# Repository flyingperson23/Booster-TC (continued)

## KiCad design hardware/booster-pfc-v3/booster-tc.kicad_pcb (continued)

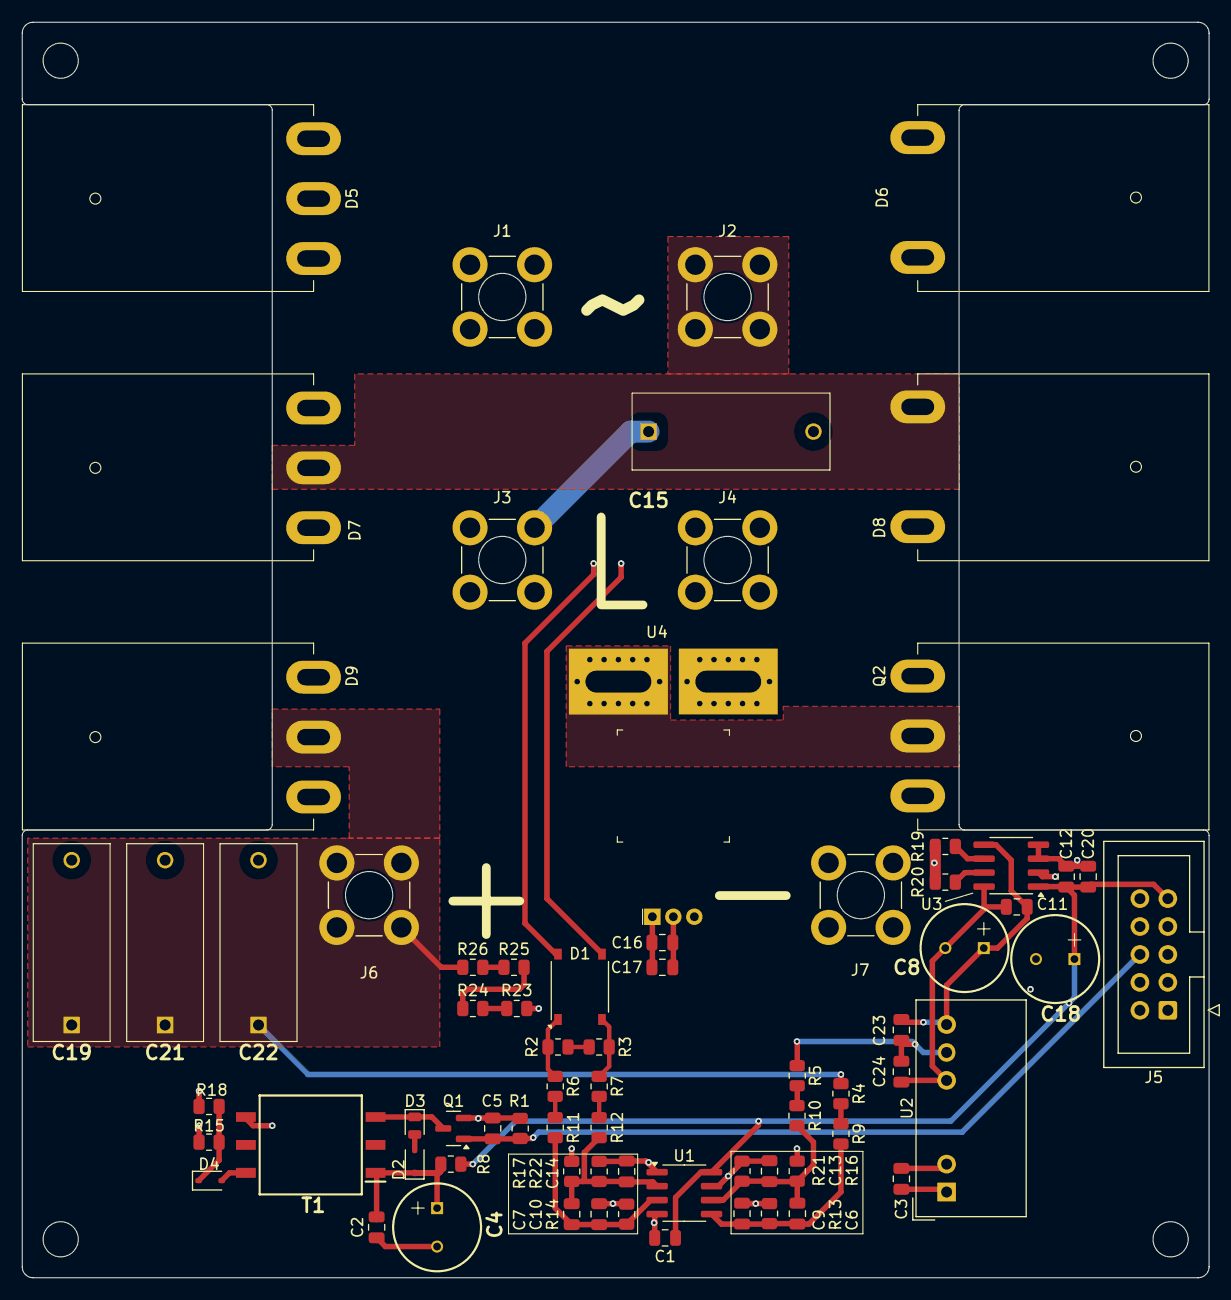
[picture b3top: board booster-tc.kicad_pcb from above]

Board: 4 copper layers, 108.0 x 114.2 mm, 77 parts (0 on the bottom side), 41 nets.

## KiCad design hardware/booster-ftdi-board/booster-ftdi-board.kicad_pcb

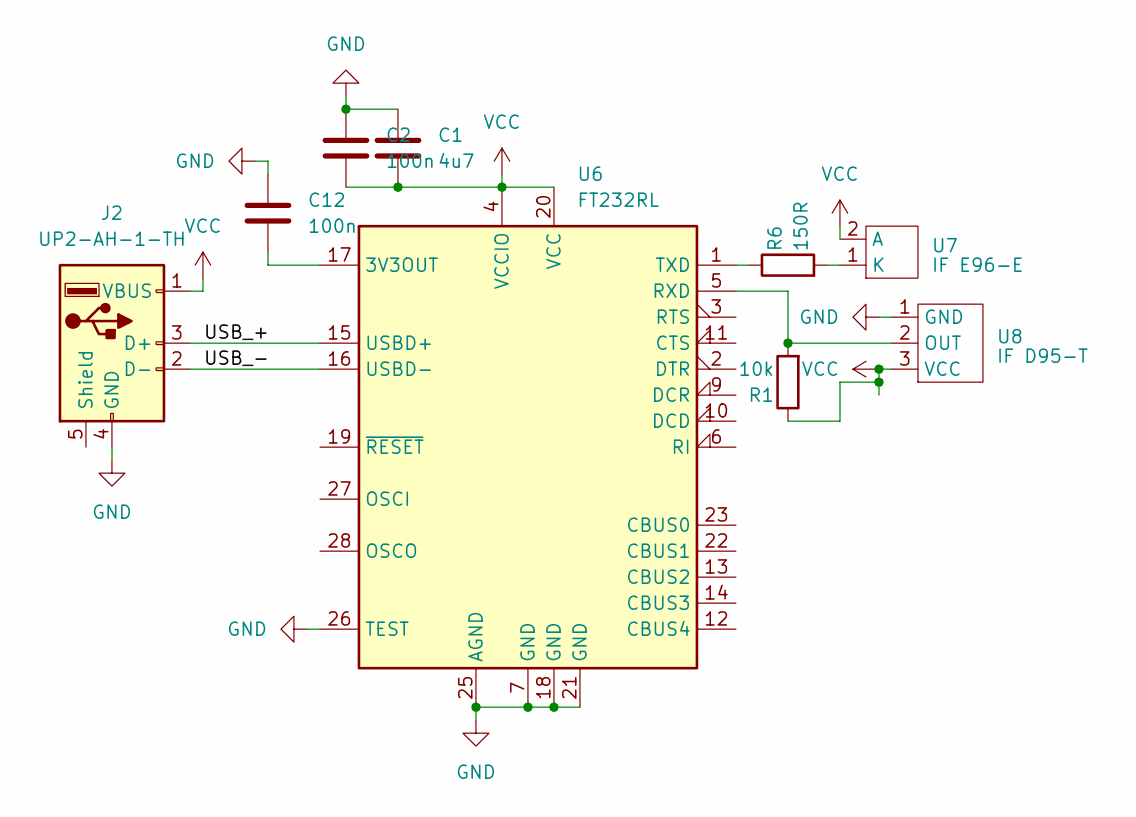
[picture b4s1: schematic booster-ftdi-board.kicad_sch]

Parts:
C1: 4u7; C_0805_2012Metric_Pad1.18x1.45mm_HandSolder
C2, C12: 100n; C_0805_2012Metric_Pad1.18x1.45mm_HandSolder
J2: UP2-AH-1-TH; USB_Male_A_UP2-AH-1-TH
R1: 10k; R_0805_2012Metric_Pad1.20x1.40mm_HandSolder
R6: 150R; R_0805_2012Metric_Pad1.20x1.40mm_HandSolder
U6: FT232RL; SSOP-28_5.3x10.2mm_P0.65mm
U7: IF E96-E; IF-E96E
U8: IF D95-T; IF-D95

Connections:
/USB_+: J2.3 (D+), U6.15 (USBD+)
/USB_-: J2.2 (D-), U6.16 (USBD-)
GND: C1.1, C2.1, C12.1, J2.4 (GND), U6.7 (GND), U6.18 (GND), U6.21 (GND), U6.25 (AGND), U6.26 (TEST), U8.1 (GND)
unnamed: C12.2, U6.17 (3V3OUT)
unnamed: R1.2, U6.5 (RXD), U8.2 (OUT)
unnamed: R6.1, U6.1 (TXD)
unnamed: R6.2, U7.1 (K)
VCC: C1.2, C2.2, J2.1 (VBUS), R1.1, U6.4 (VCCIO), U6.20 (VCC), U7.2 (A), U8.3 (VCC)

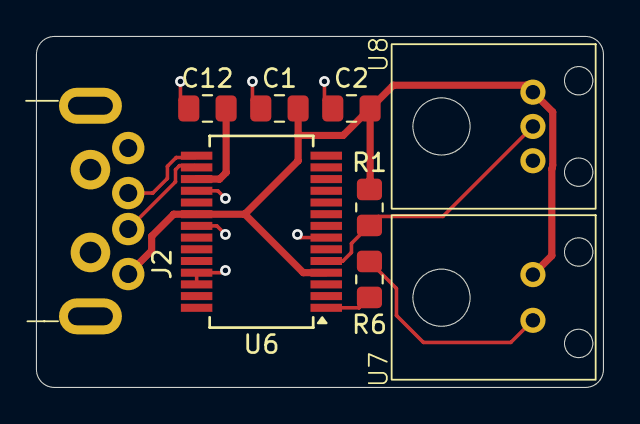
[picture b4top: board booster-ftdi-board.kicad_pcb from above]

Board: 2 copper layers, 31.5 x 19.5 mm, 9 parts (0 on the bottom side), 8 nets.

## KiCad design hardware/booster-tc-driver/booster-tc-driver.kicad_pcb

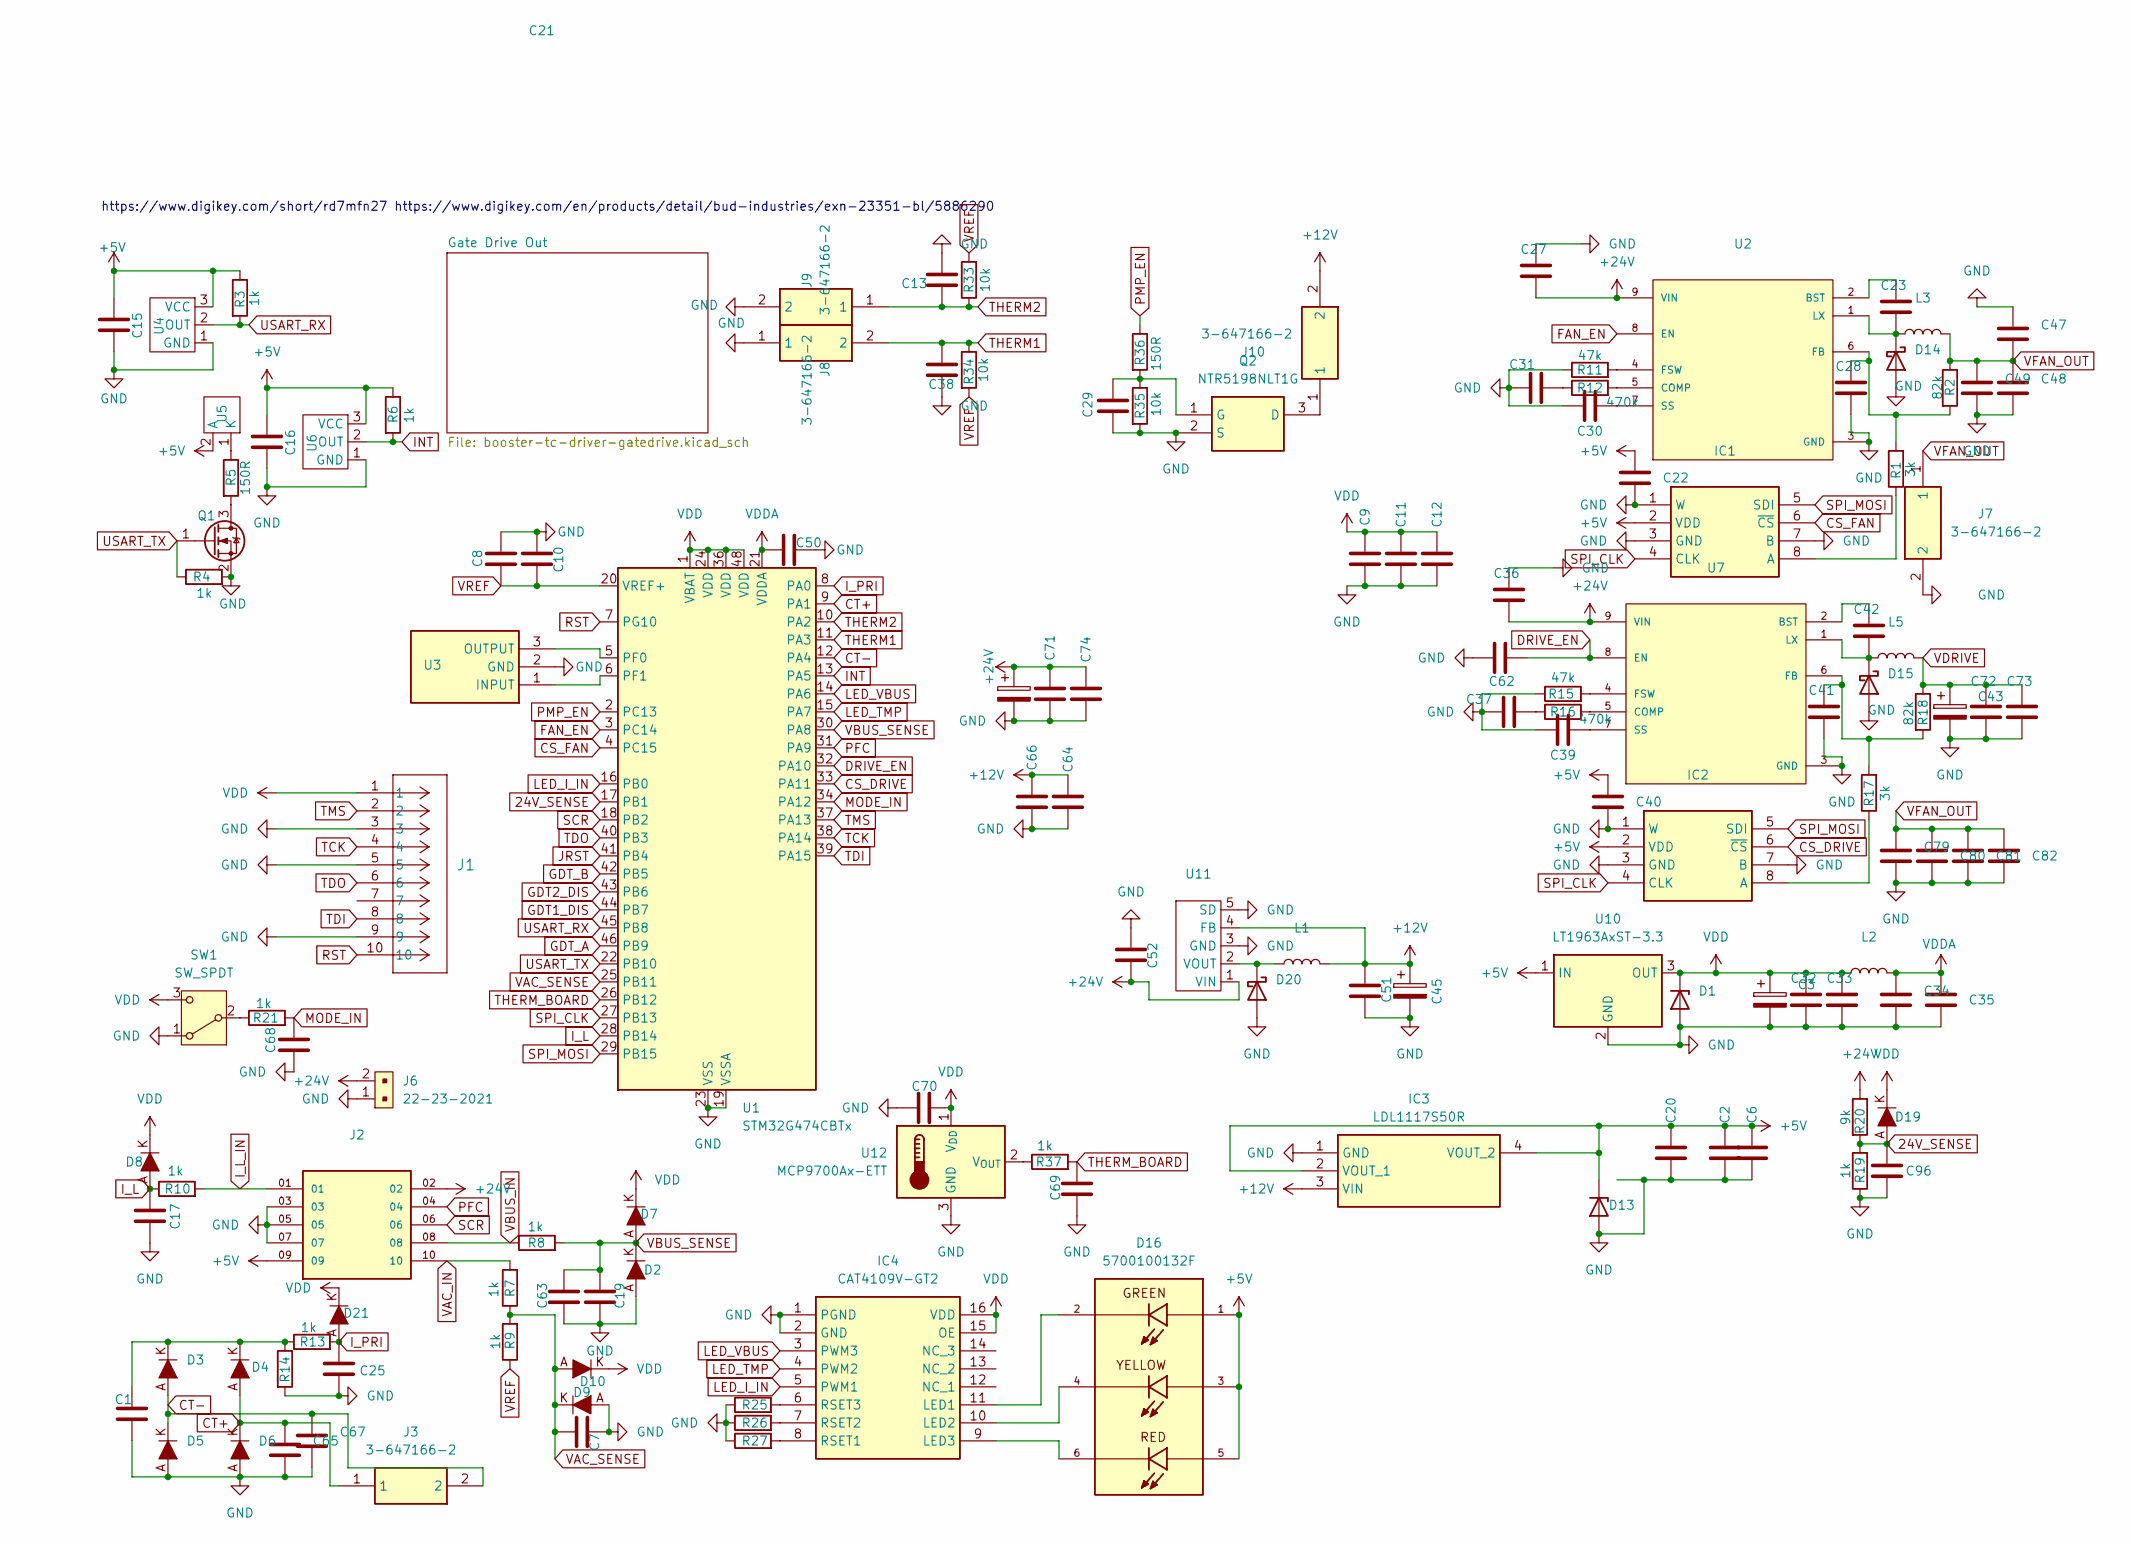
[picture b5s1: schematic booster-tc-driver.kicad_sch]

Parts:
C1, C17, C19, C25, C29, C31, C37: 1n CGA3EAC0G2A102J080AA; C_0603_1608Metric_Pad1.08x0.95mm_HandSolder
C2, C15, C16, C20, C34, C47, C48, C49, C79: 2u2 C3225X7R1H225K250AB; C_1210_3225Metric_Pad1.33x2.70mm_HandSolder
C3, C43, C45: 470u 860020474014; CAPPRD350W52D800H1300
C6, C22, C23, C27, C28, C32, C33, C36, C40, C41, C42, C51, C52, C64, C66, C70, C71, C72, C73, C74, C96: .1uf 885012208087; C_1206_3216Metric_Pad1.33x1.80mm_HandSolder
C7, C63, C69: 10n VJ0603Y103KXJAC31X; C_0603_1608Metric_Pad1.08x0.95mm_HandSolder
C8, C68: 1u C1206C105K5RACTU; C_1206_3216Metric_Pad1.33x1.80mm_HandSolder
C9, C10, C11, C12, C13, C35, C38, C50, C80, C81, C82: .1uf C0603C104K3RECTU; C_0603_1608Metric_Pad1.08x0.95mm_HandSolder
C21: 330u 860020575013; 860020575013
C30, C39, C62: 22n VJ0805Y223KBBBE31; C_0805_2012Metric_Pad1.18x1.45mm_HandSolder
C65, C67: 150p VJ0603A151JXAAC; C_0603_1608Metric_Pad1.08x0.95mm_HandSolder
D1: SMBJ3V3; DO-214AA
D2, D7, D8, D9, D10, D19, D21: MBR0530; SOD-123; MPN MBR0530
D3, D4, D5, D6: 1N5819HW-7-F; SOD-123; MPN 1N5819HW-7-F
D13: SMBJ5.0A-TR; DO-214AA
D14, D15, D20: PMEG4050EP; D_SOD-128
D16: 5700100132F; LED_5700100132F; PARTREV N
IC1, IC2: AD5160BRJZ5-RL7; SOT65P280X145-8N; Mouser Part Number 584-AD5160BRJZ5-R7
IC3: LDL1117S50R; SOT230P700X180-4N; Mouser Part Number 511-LDL1117S50R
IC4: CAT4109V-GT2; Mouser Part Number 698-CAT4109V-GT2
J1: 62201021121; CONN_62201021121_WRE
J2: EHT-105-01-S-D; SAMTEC_EHT-105-01-S-D
J3, J7, J8, J9, J10: 3-647166-2; 36471662; Mouser Part Number 571-3-647166-2
J6: 22-23-2021; PinHeader_1x2_P2.54mm_Drill1.02mm; MPN 22-23-2021
L1, L3, L5: 22u IHLP3232DZER220M5A; IND_IHLP-3232DZ_VIS-M
L2: 4u7 LQM2MPN4R7NG0L; LQM2MPN4R7NG0L
Q1: T2N7002AK; SOT-23
Q2: NTR5198NLT1G; SOT96P237X111-3N; Mouser Part Number 863-NTR5198NLT1G
R1, R17: 3k; R_0805_2012Metric_Pad1.20x1.40mm_HandSolder
R2, R18: 82k; R_0805_2012Metric_Pad1.20x1.40mm_HandSolder
R3, R4, R6, R7, R8, R9, R10, R13, R19, R21, R37: 1k; R_0805_2012Metric_Pad1.20x1.40mm_HandSolder
R5, R36: 150R; R_0805_2012Metric_Pad1.20x1.40mm_HandSolder
R11, R15: 47k; R_0805_2012Metric_Pad1.20x1.40mm_HandSolder
R12, R16: 470k; R_0805_2012Metric_Pad1.20x1.40mm_HandSolder
R14: 2R2 35222R2JT; R_2512_6332Metric_Pad1.40x3.35mm_HandSolder
R20: 9k; R_0805_2012Metric_Pad1.20x1.40mm_HandSolder
R25, R26, R27: 24k9 CRCW060324K9FKEA; R_0603_1608Metric_Pad0.98x0.95mm_HandSolder
R33, R34, R35: 10k; R_0805_2012Metric_Pad1.20x1.40mm_HandSolder
SW1: SW_SPDT; B12JV
U1: STM32G474CBTx; LQFP-48_7x7mm_P0.5mm
U2, U7: AOZ1284PI; SOIC-8-1EP_3.9x4.9mm_P1.27mm_EP2.29x3mm; PARTREV 0.5
U3: CSTNE8M00G550000R0; CSTNE16M0V530000R0; Mouser Part Number 81-CSTNE8M00G550000R
U4, U6: IF-D95T << must be T; IF-D95
U5: IF-E96E
U10: LT1963AxST-3.3; SOT-223-3_TabPin2
U11: AP1501A-12K5G-13; TO-263-5_TabPin3
U12: MCP9700Ax-ETT; SOT-23

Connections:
24V_SENSE: C96.1, D19.A, R19.2, R20.2, U1.17 (PB1)
+5V: C2.1, C6.1, C15.1, C16.1, C20.1, C22.2, C40.2, D13.1 (K), D16.1, D16.3, D16.5, IC1.2 (VDD), IC2.2 (VDD), IC3.2 (VOUT_1), IC3.4 (VOUT_2), J2.09, R3.1, R6.1, U4.3 (VCC), U5.2 (A), U6.3 (VCC), U10.1 (IN)
+12V: C45.1, C51.1, C64.1, C66.1, IC3.3 (VIN), J10.2, L1.2, U11.4 (FB); also elsewhere on the board
+24V: C21.1, C27.2, C36.2, C52.2, C71.1, C74.1, J2.02, J6.2, R20.1, U2.9 (VIN), U7.9 (VIN), U11.1 (VIN)
CS_DRIVE: IC2.6 (~CS), U1.33 (PA11)
CS_FAN: IC1.6 (~CS), U1.4 (PC15)
CT+: C65.1, D4.A, D6.K, J3.1, U1.9 (PA1)
CT-: C67.1, D3.A, D5.K, J3.2, U1.12 (PA4)
DRIVE_EN: C62.1, U1.32 (PA10), U7.8 (EN)
FAN_EN: U1.3 (PC14), U2.8 (EN)
GDT1_DIS: U1.44 (PB7); also elsewhere on the board
GDT2_DIS: U1.43 (PB6); also elsewhere on the board
GDT_A: U1.46 (PB9); also elsewhere on the board
GDT_B: U1.42 (PB5); also elsewhere on the board
GND: C1.2, C2.2, C3.2, C6.2, C7.2, C8.1, C9.2, C10.1, C11.2, C12.2, C13.2, C15.2, C16.2, C17.2, C19.2, C20.2, C21.2, C22.1, C25.2, C27.1, C28.2, C29.2, C30.2, C31.1, C32.2, C33.2, C34.2, C35.1, C36.1, C37.1, C38.1, C39.2, C40.1, C41.2, C43.2, C45.2, C47.1, C48.2, C49.2, C50.2, C51.2, C52.1, C62.2, C63.2, C64.2, C65.2, C66.2, C67.2, C68.2, C69.2, C70.1, C71.2, C72.2, C73.2, C74.2, C79.2, C80.1, C81.1, C82.1, C96.2, D1.2 (A), D2.A, D5.A, D6.A, D9.A, D13.2 (A), D14.2 (A), D15.2 (A), D20.2 (A), IC1.1 (W), IC1.3 (GND), IC1.7 (B), IC2.1 (W), IC2.3 (GND), IC2.7 (B), IC3.1 (GND), IC4.1 (PGND), IC4.2 (GND), J1.3, J1.5, J1.9, J2.03, J2.05, J2.07, J6.1, J7.2, J8.2, J9.1, Q1.2 (S), Q2.2 (S), R4.2, R11.1, R14.2, R15.1, R19.1, R25.1, R26.1, R27.1, R35.2, SW1.1 (A), U1.19 (VSSA), U1.23 (VSS), U1.35 (VSS), U1.47 (VSS), U2.3 (GND), U3.2 (GND), U4.1 (GND), U6.1 (GND), U7.3 (GND), U10.2 (GND), U11.3 (GND), U11.5 (SD), U12.3 (GND); also elsewhere on the board
INT: R6.2, U1.13 (PA5), U6.2 (OUT)
I_L: C17.1, D8.A, R10.1, U1.28 (PB14)
I_L_IN: J2.01, R10.2
I_PRI: C25.1, D21.A, R13.2, U1.8 (PA0)
JRST: U1.41 (PB4)
LED_I_IN: IC4.5 (PWM1), U1.16 (PB0)
LED_TMP: IC4.4 (PWM2), U1.15 (PA7)
LED_VBUS: IC4.3 (PWM3), U1.14 (PA6)
MODE_IN: C68.1, R21.2, U1.34 (PA12)
unnamed: C1.1, D3.K, D4.K, R13.1, R14.1
unnamed: C31.2, R12.1
unnamed: C37.2, R16.1
unnamed: C23.2, D14.1 (K), L3.1, U2.1 (LX)
unnamed: C42.2, D15.1 (K), L5.1, U7.1 (LX)
unnamed: D20.1 (K), L1.1, U11.2 (VOUT)
unnamed: IC1.8 (A), R1.1
unnamed: IC2.8 (A), R17.1
unnamed: D16.2, IC4.11 (LED1)
unnamed: D16.4, IC4.10 (LED2)
unnamed: D16.6, IC4.9 (LED3)
unnamed: IC4.8 (RSET1), R27.2
unnamed: IC4.7 (RSET2), R26.2
unnamed: IC4.6 (RSET3), R25.2
unnamed: Q1.3 (D), R5.2
unnamed: J10.1, Q2.3 (D)
unnamed: C29.1, Q2.1 (G), R35.1, R36.2
unnamed: R21.1, SW1.2 (B)
unnamed: U1.5 (PF0), U3.3 (OUTPUT)
unnamed: U1.6 (PF1), U3.1 (INPUT)
unnamed: C23.1, U2.2 (BST)
unnamed: R12.2, U2.5 (COMP)
unnamed: C28.1, R1.2, R2.2, U2.6 (FB)
unnamed: R11.2, U2.4 (FSW)
unnamed: C30.1, U2.7 (SS)
unnamed: R5.1, U5.1 (K)
unnamed: C42.1, U7.2 (BST)
unnamed: R16.2, U7.5 (COMP)
unnamed: C41.1, R17.2, R18.2, U7.6 (FB)
unnamed: R15.2, U7.4 (FSW)
unnamed: C39.1, U7.7 (SS)
unnamed: R37.1, U12.2 (V_{OUT})
PFC: J2.04, U1.31 (PA9)
PMP_EN: R36.1, U1.2 (PC13)
RST: J1.10, U1.7 (PG10)
SCR: J2.06, U1.18 (PB2)
SPI_CLK: IC1.4 (CLK), IC2.4 (CLK), U1.27 (PB13)
SPI_MOSI: IC1.5 (SDI), IC2.5 (SDI), U1.29 (PB15)
TCK: J1.4, U1.38 (PA14)
TDI: J1.8, U1.39 (PA15)
TDO: J1.6, U1.40 (PB3)
THERM1: C38.2, J9.2, R34.1, U1.11 (PA3)
THERM2: C13.1, J8.1, R33.1, U1.10 (PA2)
THERM_BOARD: C69.1, R37.2, U1.26 (PB12)
TMS: J1.2, U1.37 (PA13)
USART_RX: R3.2, U1.45 (PB8), U4.2 (OUT)
USART_TX: Q1.1 (G), R4.1, U1.22 (PB10)
VAC_IN: J2.10, R7.2
VAC_SENSE: C7.1, D9.K, D10.A, R7.1, R9.2, U1.25 (PB11)
VBUS_IN: J2.08, R8.1
VBUS_SENSE: C19.1, C63.1, D2.K, D7.A, R8.2, U1.30 (PA8)
VDD: C3.1, C9.1, C11.1, C12.1, C32.1, C33.1, C70.2, D1.1 (K), D7.K, D8.K, D10.K, D19.K, D21.K, IC4.15 (OE), IC4.16 (VDD), J1.1, L2.1, SW1.3 (C), U1.1 (VBAT), U1.24 (VDD), U1.36 (VDD), U1.48 (VDD), U10.3 (OUT), U12.1 (V_{DD})
VDDA: C34.1, C35.2, C50.1, L2.2, U1.21 (VDDA)
VDRIVE: C43.1, C72.1, C73.1, L5.2, R18.1; also elsewhere on the board
VFAN_OUT: C47.2, C48.1, C49.1, C79.1, C80.2, C81.2, C82.2, J7.1, L3.2, R2.1
VREF: C8.2, C10.2, R9.1, R33.2, R34.2, U1.20 (VREF+)

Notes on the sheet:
https://www.digikey.com/short/rd7mfn27 https://www.digikey.com/en/products/detail/bud-industries/exn-23351-bl/5886290

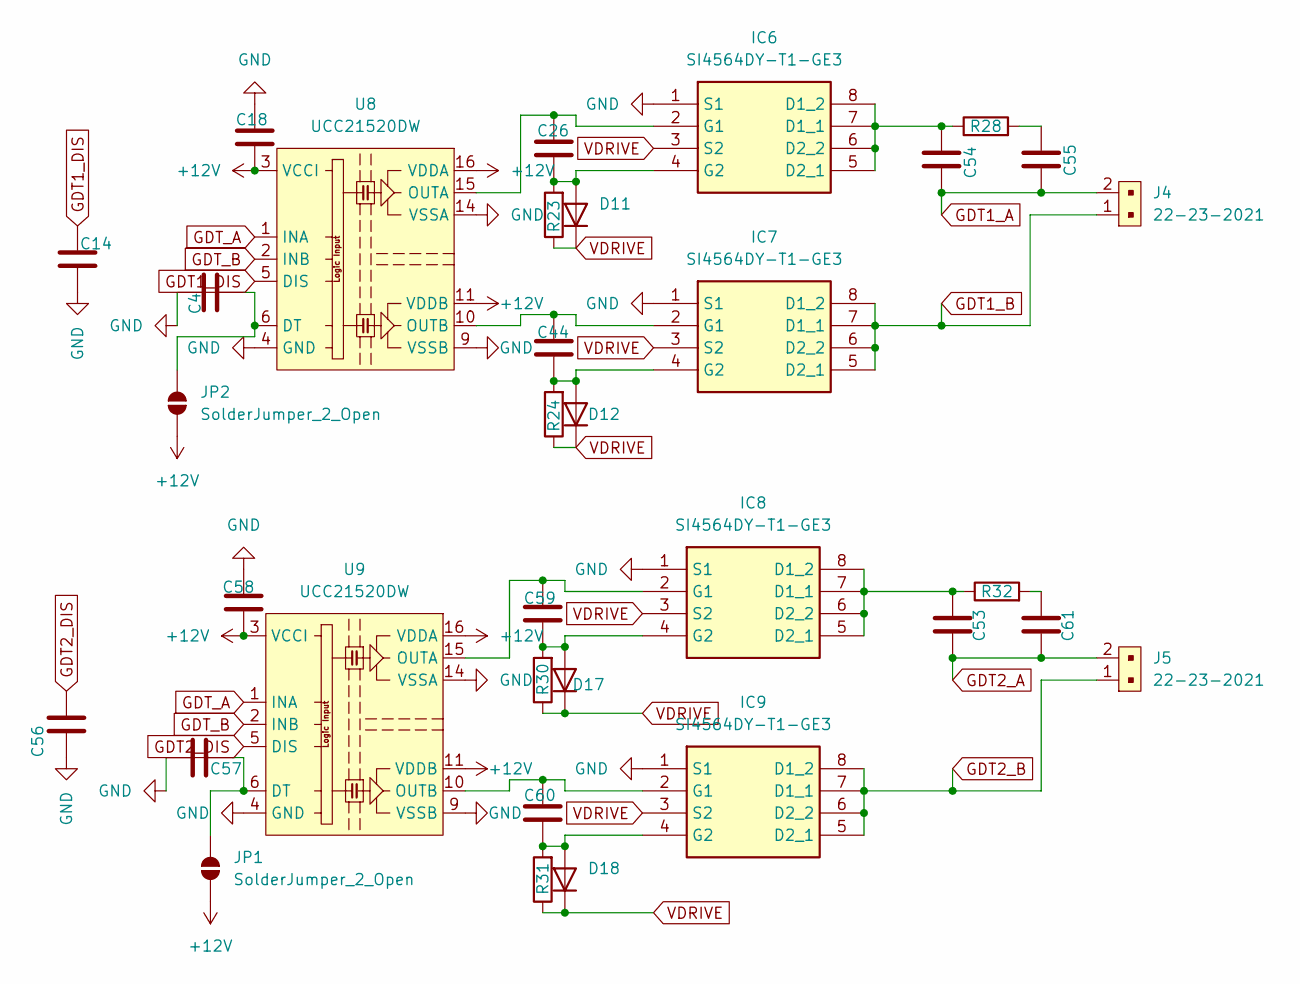
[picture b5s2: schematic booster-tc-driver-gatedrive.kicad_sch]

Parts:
C4, C57: 22n VJ0805Y223KBBBE31; C_0805_2012Metric_Pad1.18x1.45mm_HandSolder
C14, C56: 1n CGA3EAC0G2A102J080AA; C_0603_1608Metric_Pad1.08x0.95mm_HandSolder
C18, C26, C44, C58, C59, C60: .1uf 885012208087; C_1206_3216Metric_Pad1.33x1.80mm_HandSolder
C53, C54: 2u2 C3225X7R1H225K250AB; C_1210_3225Metric_Pad1.33x2.70mm_HandSolder
C55, C61: 1u C1206C105K5RACTU; C_1206_3216Metric_Pad1.33x1.80mm_HandSolder
D11, D12, D17, D18: MCL4148; D_MicroMELF
IC6, IC7, IC8, IC9: SI4564DY-T1-GE3; SOIC127P600X175-8N; Mouser Part Number 781-SI4564DY-T1-GE3
J4, J5: 22-23-2021; PinHeader_1x2_P2.54mm_Drill1.02mm; MPN 22-23-2021
JP1, JP2: SolderJumper_2_Open; SolderJumper-2_P1.3mm_Open_RoundedPad1.0x1.5mm
R23, R24, R30, R31: 1k MCU0805MD1051BP500; R_0805_2012Metric_Pad1.20x1.40mm_HandSolder
R28, R32: 15R CRCW121015R0JNEAHP; R_1210_3225Metric_Pad1.30x2.65mm_HandSolder
U8, U9: UCC21520DW; SOIC-16W_7.5x10.3mm_P1.27mm

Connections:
+12V: C18.2, C58.2, JP1.1 (A), JP2.1 (A), U8.3 (VCCI), U8.8 (VCCI), U8.11 (VDDB), U8.16 (VDDA), U9.3 (VCCI), U9.8 (VCCI), U9.11 (VDDB), U9.16 (VDDA); also elsewhere on the board
GDT1_A: C54.2, C55.2, J4.2
GDT1_B: IC7.5 (D2_1), IC7.6 (D2_2), IC7.7 (D1_1), IC7.8 (D1_2), J4.1
GDT1_DIS: C14.2, U8.5 (DIS); also elsewhere on the board
GDT2_A: C53.2, C61.2, J5.2
GDT2_B: IC9.5 (D2_1), IC9.6 (D2_2), IC9.7 (D1_1), IC9.8 (D1_2), J5.1
GDT2_DIS: C56.2, U9.5 (DIS); also elsewhere on the board
GDT_A: U8.1 (INA), U9.1 (INA); also elsewhere on the board
GDT_B: U8.2 (INB), U9.2 (INB); also elsewhere on the board
GND: C4.2, C14.1, C18.1, C56.1, C57.2, C58.1, IC6.1 (S1), IC7.1 (S1), IC8.1 (S1), IC9.1 (S1), U8.4 (GND), U8.9 (VSSB), U8.14 (VSSA), U9.4 (GND), U9.9 (VSSB), U9.14 (VSSA); also elsewhere on the board
unnamed: C55.1, R28.2
unnamed: C61.1, R32.2
unnamed: C26.2, D11.2 (A), IC6.4 (G2), R23.2
unnamed: C44.2, D12.2 (A), IC7.4 (G2), R24.2
unnamed: C59.2, D17.2 (A), IC8.4 (G2), R30.2
unnamed: C60.2, D18.2 (A), IC9.4 (G2), R31.2
unnamed: C54.1, IC6.5 (D2_1), IC6.6 (D2_2), IC6.7 (D1_1), IC6.8 (D1_2), R28.1
unnamed: C26.1, IC6.2 (G1), U8.15 (OUTA)
unnamed: C44.1, IC7.2 (G1), U8.10 (OUTB)
unnamed: C53.1, IC8.5 (D2_1), IC8.6 (D2_2), IC8.7 (D1_1), IC8.8 (D1_2), R32.1
unnamed: C59.1, IC8.2 (G1), U9.15 (OUTA)
unnamed: C60.1, IC9.2 (G1), U9.10 (OUTB)
unnamed: C57.1, JP1.2 (B), U9.6 (DT)
unnamed: C4.1, JP2.2 (B), U8.6 (DT)
VDRIVE: D11.1 (K), D12.1 (K), D17.1 (K), D18.1 (K), IC6.3 (S2), IC7.3 (S2), IC8.3 (S2), IC9.3 (S2), R23.1, R24.1, R30.1, R31.1; also elsewhere on the board

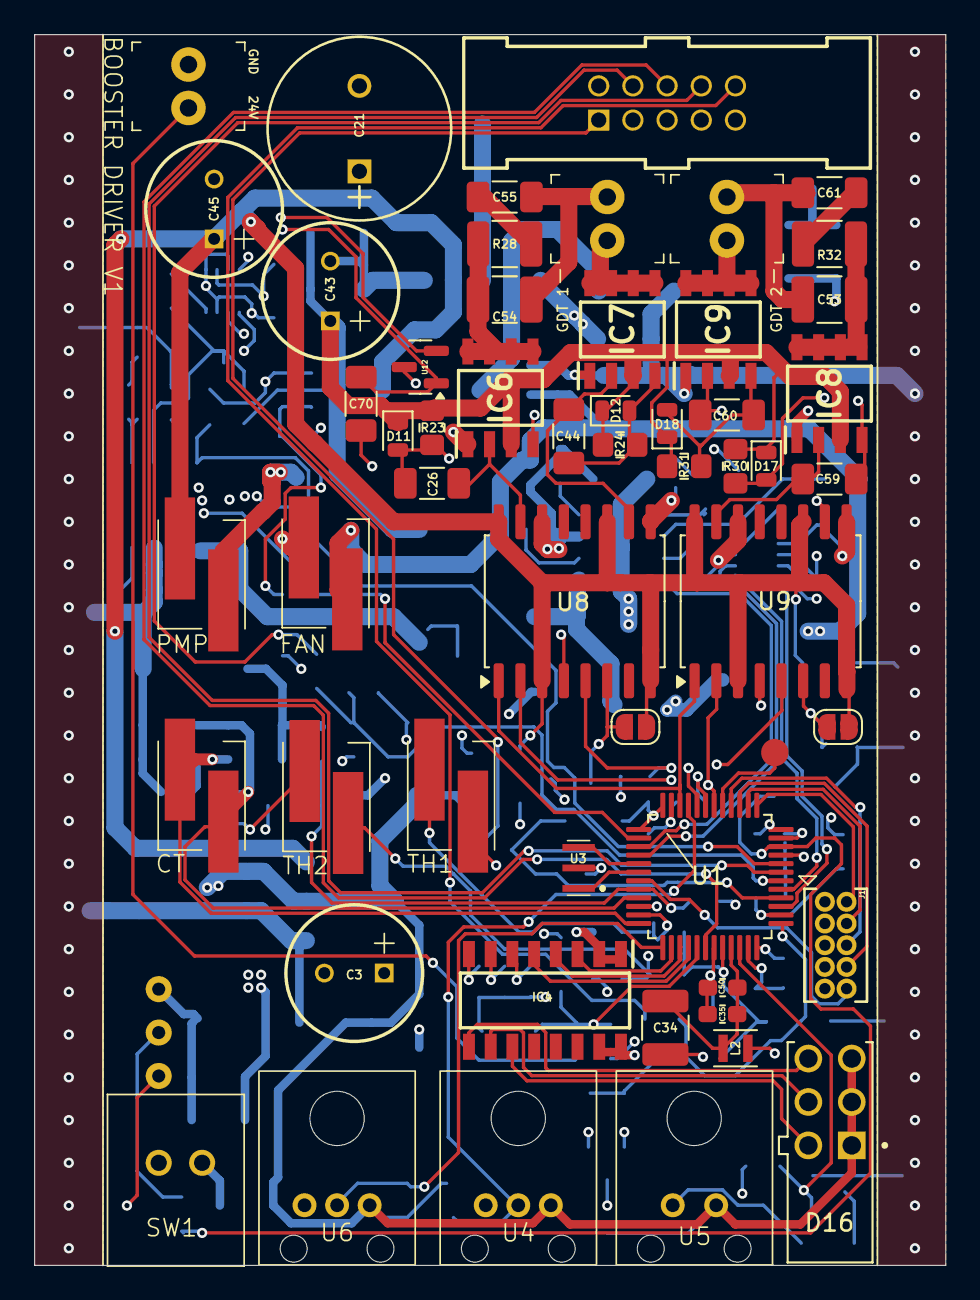
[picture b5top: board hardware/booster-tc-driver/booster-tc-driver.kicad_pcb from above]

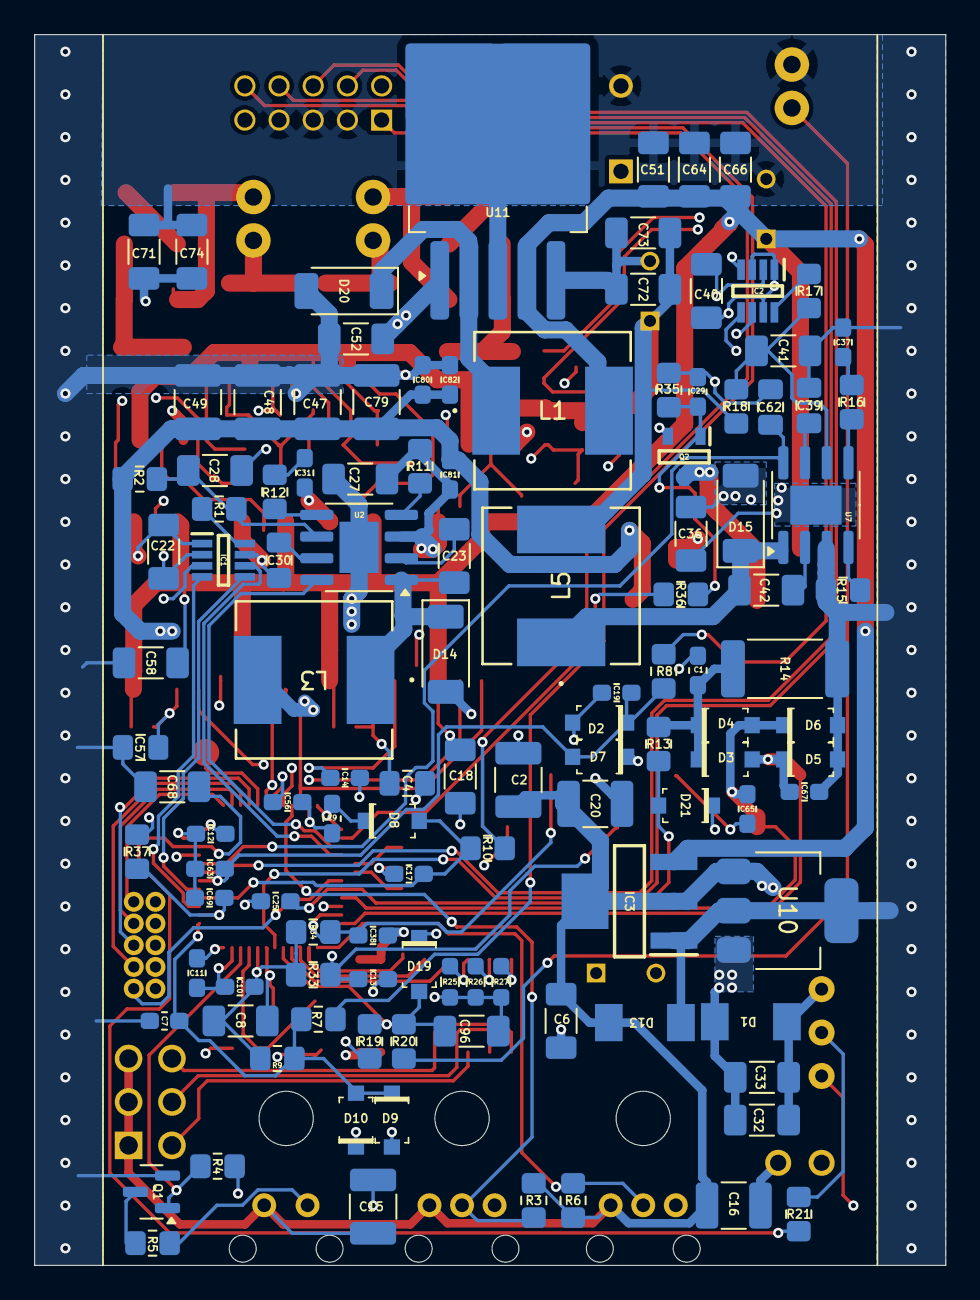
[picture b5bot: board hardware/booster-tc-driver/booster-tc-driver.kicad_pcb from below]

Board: 4 copper layers, 53.3 x 72.0 mm, 171 parts (117 on the bottom side), 97 nets.

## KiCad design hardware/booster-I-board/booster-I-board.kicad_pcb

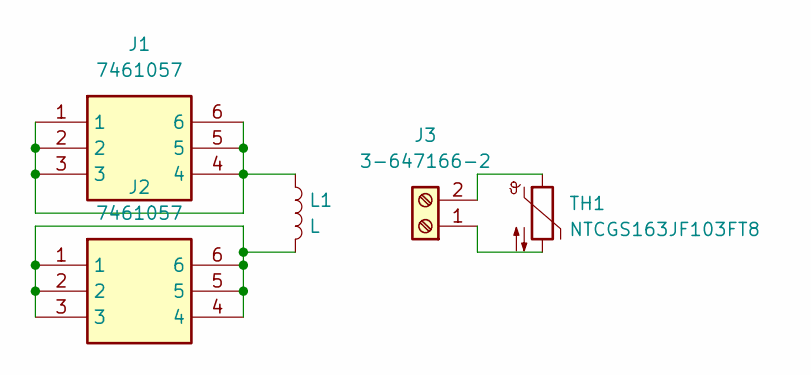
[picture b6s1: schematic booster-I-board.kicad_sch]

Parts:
J1, J2: 7461057; Mouser Part Number 710-7461057
J3: 3-647166-2; 36471662
L1: L; WE-TORPFC_T37_D53H28
TH1: NTCGS163JF103FT8; R_0603_1608Metric_Pad0.98x0.95mm_HandSolder

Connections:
unnamed: J1.1, J1.2, J1.3, J1.4, J1.5, J1.6, L1.1
unnamed: J2.1, J2.2, J2.3, J2.4, J2.5, J2.6, L1.2
unnamed: J3.1, TH1.2
unnamed: J3.2, TH1.1

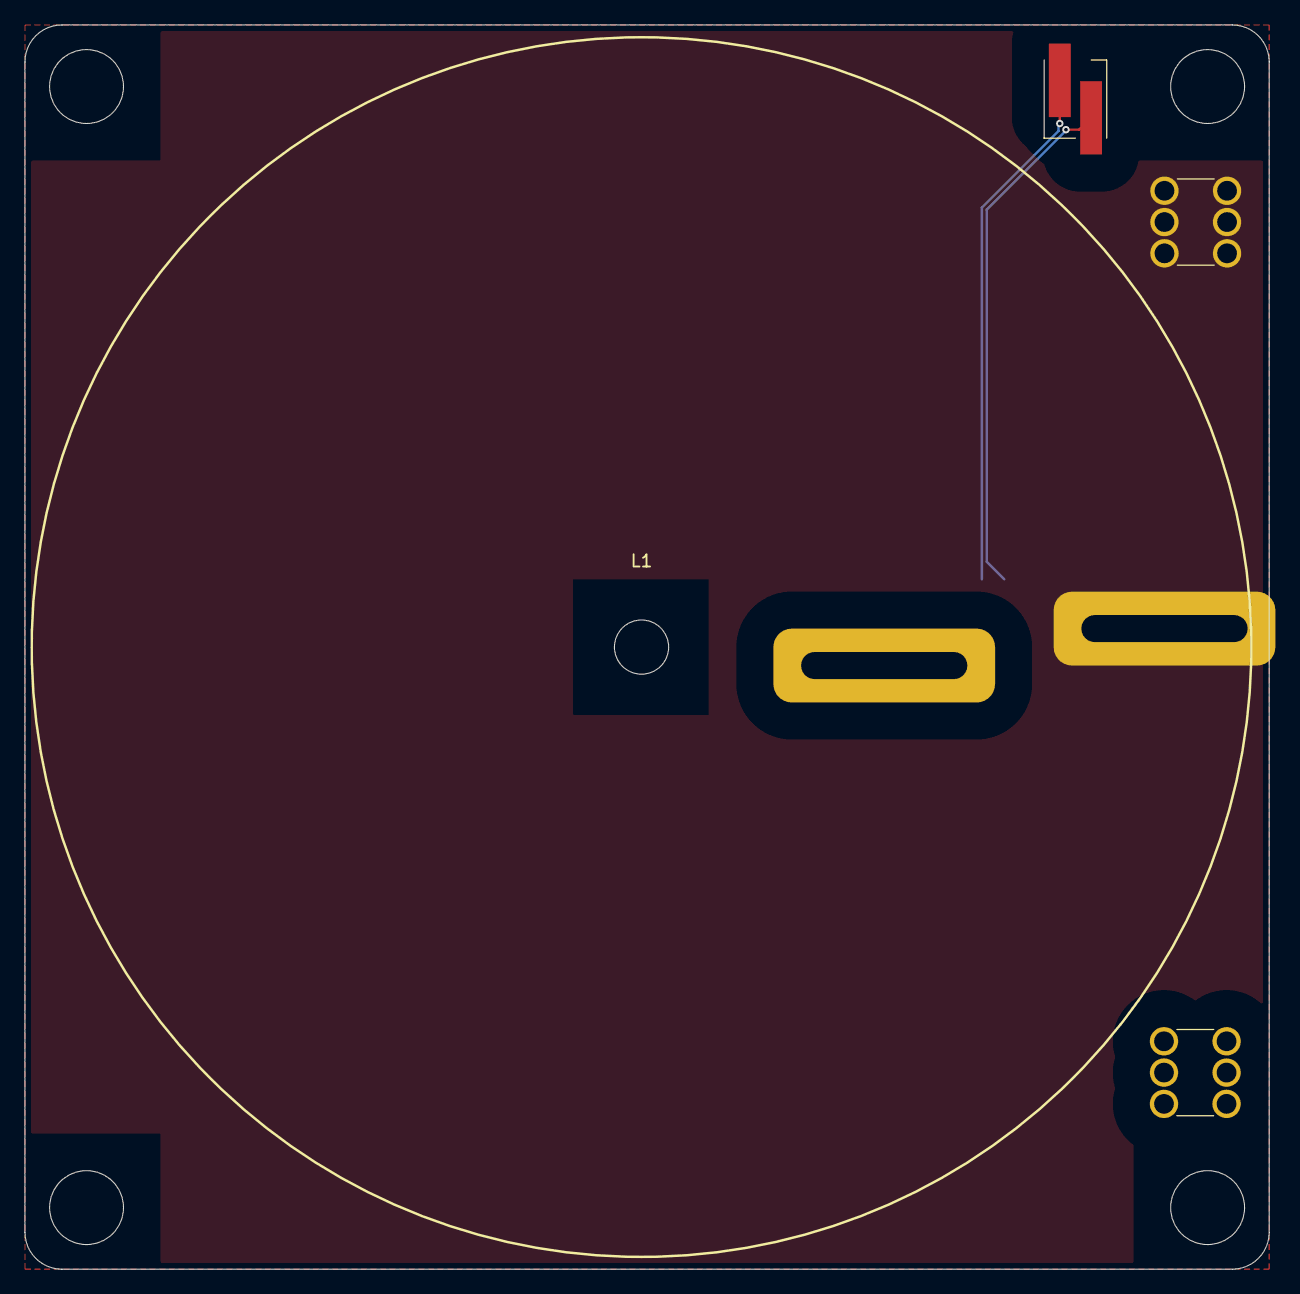
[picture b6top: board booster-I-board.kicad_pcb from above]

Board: 2 copper layers, 101.0 x 101.0 mm, 5 parts (1 on the bottom side), 4 nets.

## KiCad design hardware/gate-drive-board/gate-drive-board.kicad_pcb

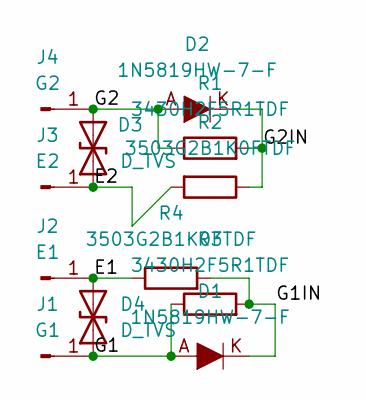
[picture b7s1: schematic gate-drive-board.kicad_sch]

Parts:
D1, D2: 1N5819HW-7-F; SOD-123; MPN 1N5819HW-7-F
D3, D4: D_TVS; D_SMC_Handsoldering
J1: G1; 3544-Spade
J2: E1; 3544-Spade
J3: E2; 3544-Spade
J4: G2; 3544-Spade
R1, R3: 3430H2F5R1TDF; R_1020_2550Metric_Pad1.33x5.20mm_HandSolder
R2, R4: 3503G2B1K0FTDF; R_1206_3216Metric_Pad1.30x1.75mm_HandSolder

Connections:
/E1: D4.2 (A2), J2.1, R4.1
/E2: D3.1 (A1), J3.1, R2.2
/G1: D1.A, D4.1 (A1), J1.1, R3.1
/G1IN: D1.K, R3.2, R4.2
/G2: D2.A, D3.2 (A2), J4.1, R1.1
/G2IN: D2.K, R1.2, R2.1

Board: 2 copper layers, 12 parts (0 on the bottom side), 6 nets, no tracks yet.

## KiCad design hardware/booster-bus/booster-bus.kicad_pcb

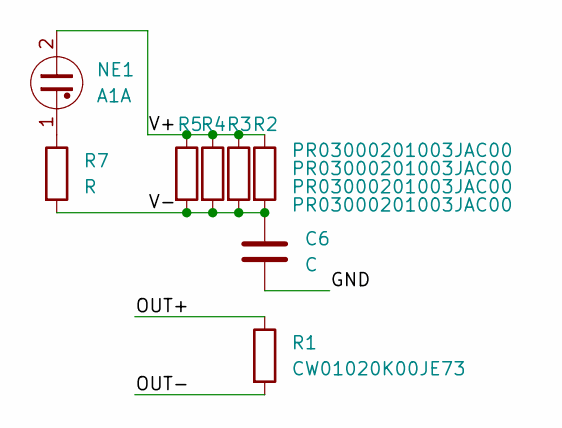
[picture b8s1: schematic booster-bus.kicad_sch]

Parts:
C6: C; ACX-MKP-0u47-630VDC
NE1: A1A; NEON-A1A
R1: CW01020K00JE73
R2, R3, R4, R5: PR03000201003JAC00
R7: R; R_Axial_DIN0207_L6.3mm_D2.5mm_P7.62mm_Horizontal

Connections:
/GND: C6.2
/OUT+: R1.1
/OUT-: R1.2
/V+: NE1.2, R2.1, R3.1, R4.1, R5.1
/V-: C6.1, R2.2, R3.2, R4.2, R5.2, R7.2
unnamed: NE1.1, R7.1

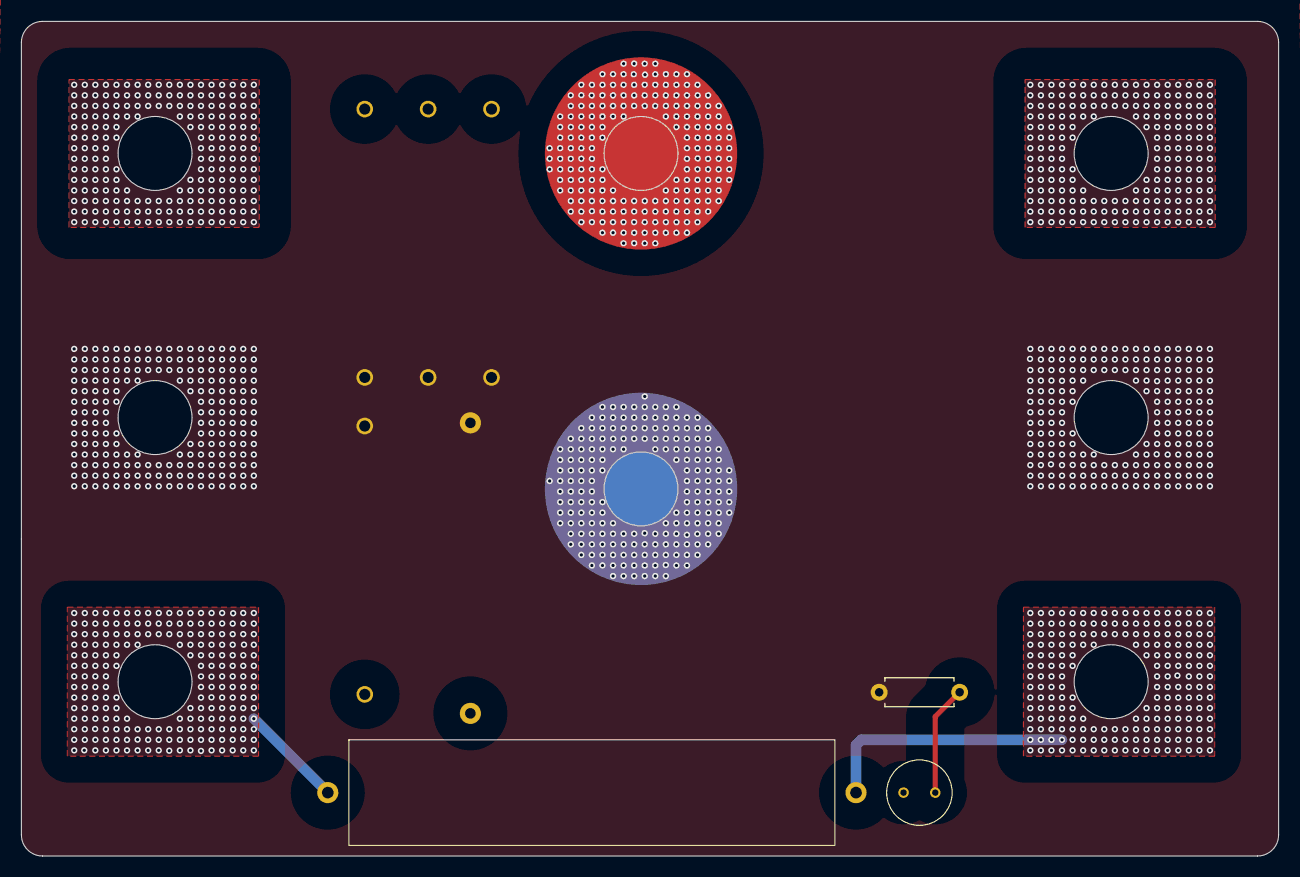
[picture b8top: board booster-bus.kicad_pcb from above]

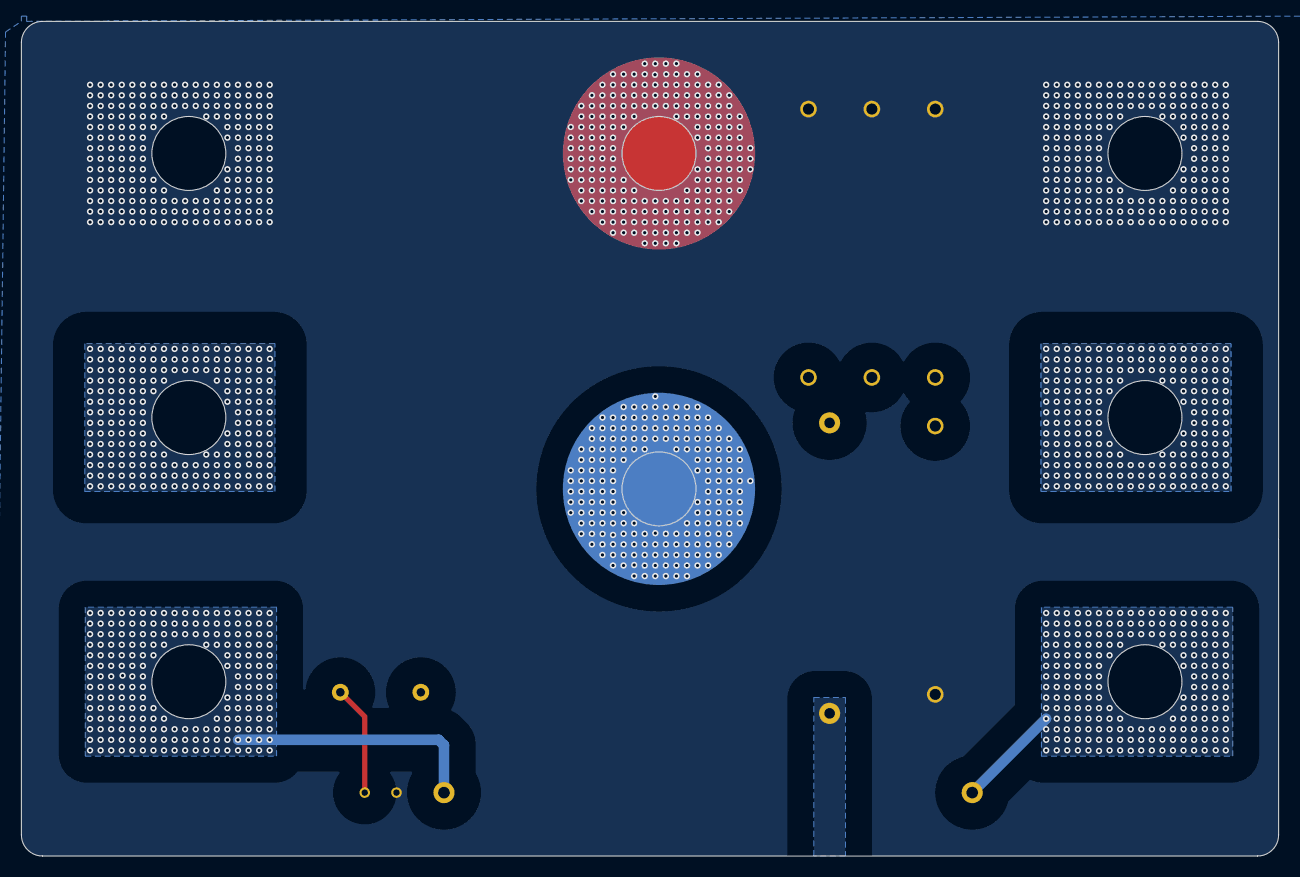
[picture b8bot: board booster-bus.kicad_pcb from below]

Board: 2 copper layers, 119.0 x 79.0 mm, 8 parts (5 on the bottom side), 3 nets.

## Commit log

2024-07-02 add hw
2024-07-02 clock+tterm
2024-07-02 pin assignments
2024-07-06 software meddling
2024-07-08 driver pcb
2024-07-12 driver board+code
2024-07-12 driver board work
2024-07-15 silkscreen + software cleanup
2024-07-15 schematic cleanup
2024-07-17 software work
2024-07-19 changed pin assignments, improved hardware
2024-07-31 ftdi board + random stuff
2024-08-01 driver work
2024-08-20 Migrate to new version
2024-08-21 timing work
2024-09-24 v2 work
2024-10-04 driver v2 work
2024-10-21 pcb work
2024-10-21 start v3
2024-10-24 v3 front silkscreen
2024-11-02 pfc v3
2024-11-03 pfc v3 finalized
